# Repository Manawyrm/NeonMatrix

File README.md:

NeonMatrix
=============================

#### Overview

The NeonMatrix 8x8 matrix uses common neon indicator bulbs to display simple graphics.  
They can be chained and controlled directly via SPI.  

Operating voltage is about ~70V AC.  
The circuit is **pretty dangerous**, all neon bulbs have high voltages on their legs, the 74HC595 shift registers are floating at mains/AC potential.  
Safe data in/output is realized through 3 ADUM1200 digital isolator ICs and one B0505S DC-DC isolating converter. 

#### Additional info

[Firmware](https://github.com/Manawyrm/NeonMatrix-Firmware)  
[Schematic](https://github.com/Manawyrm/NeonMatrix/blob/master/Schematic.pdf)

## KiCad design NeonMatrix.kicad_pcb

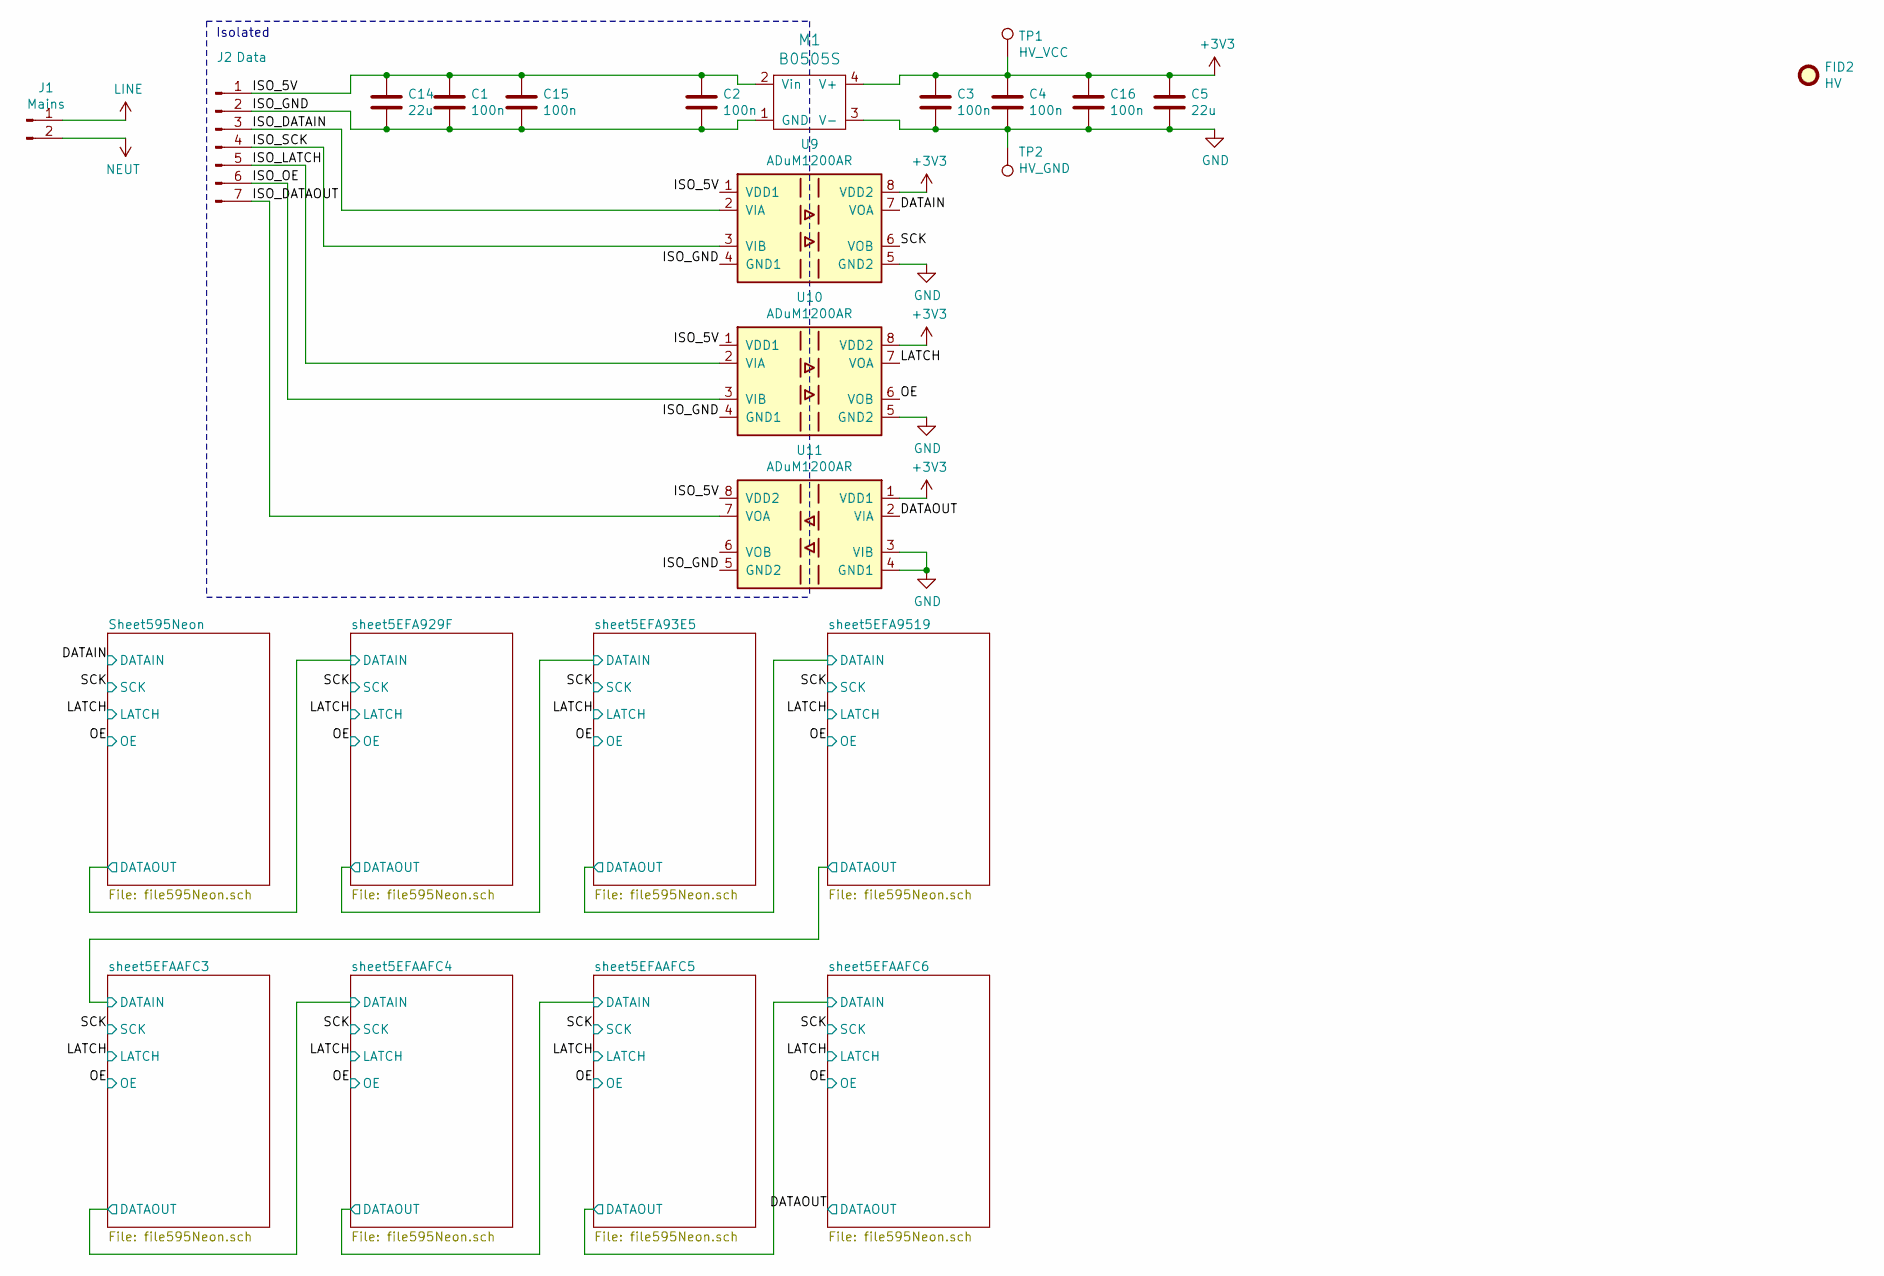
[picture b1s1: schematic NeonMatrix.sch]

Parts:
C1, C2, C3, C4, C15, C16: 100n; C_0805_2012Metric; LCSC C49678
C5, C14: 22u; C_0805_2012Metric; LCSC C45783
FID2: HV; Symbol_HighVoltage_Type1_CopperTop_Big
J1: Mains; TerminalBlock_RND_205-00001_1x02_P5.00mm_Horizontal
J2: Data; PinHeader_1x07_P2.54mm_Vertical
M1: B0505S; M_DCDC_SIP4
TP1: HV_VCC; TestPoint_Pad_2.0x2.0mm
TP2: HV_GND; TestPoint_Pad_2.0x2.0mm
U9, U10, U11: ADuM1200AR; SOIC-8_3.9x4.9mm_P1.27mm; LCSC C15219

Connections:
+3V3: C3.1, C4.1, C5.1, C16.1, M1.4 (V+), TP1.1, U9.8 (VDD2), U10.8 (VDD2), U11.1 (VDD1); also elsewhere on the board
/DATAIN: U9.7 (VOA); also elsewhere on the board
/DATAOUT: U11.2 (VIA); also elsewhere on the board
/ISO_5V: C1.1, C2.1, C14.1, C15.1, J2.1, M1.2 (Vin), U9.1 (VDD1), U10.1 (VDD1), U11.8 (VDD2)
/ISO_DATAIN: J2.3, U9.2 (VIA)
/ISO_DATAOUT: J2.7, U11.7 (VOA)
/ISO_GND: C1.2, C2.2, C14.2, C15.2, J2.2, M1.1 (GND), U9.4 (GND1), U10.4 (GND1), U11.5 (GND2)
/ISO_LATCH: J2.5, U10.2 (VIA)
/ISO_OE: J2.6, U10.3 (VIB)
/ISO_SCK: J2.4, U9.3 (VIB)
/LATCH: U10.7 (VOA); also elsewhere on the board
/OE: U10.6 (VOB); also elsewhere on the board
/SCK: U9.6 (VOB); also elsewhere on the board
GND: C3.2, C4.2, C5.2, C16.2, J1.2, M1.3 (V-), TP2.1, U9.5 (GND2), U10.5 (GND2), U11.3 (VIB), U11.4 (GND1); also elsewhere on the board
LINE: J1.1; also elsewhere on the board

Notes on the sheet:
Isolated

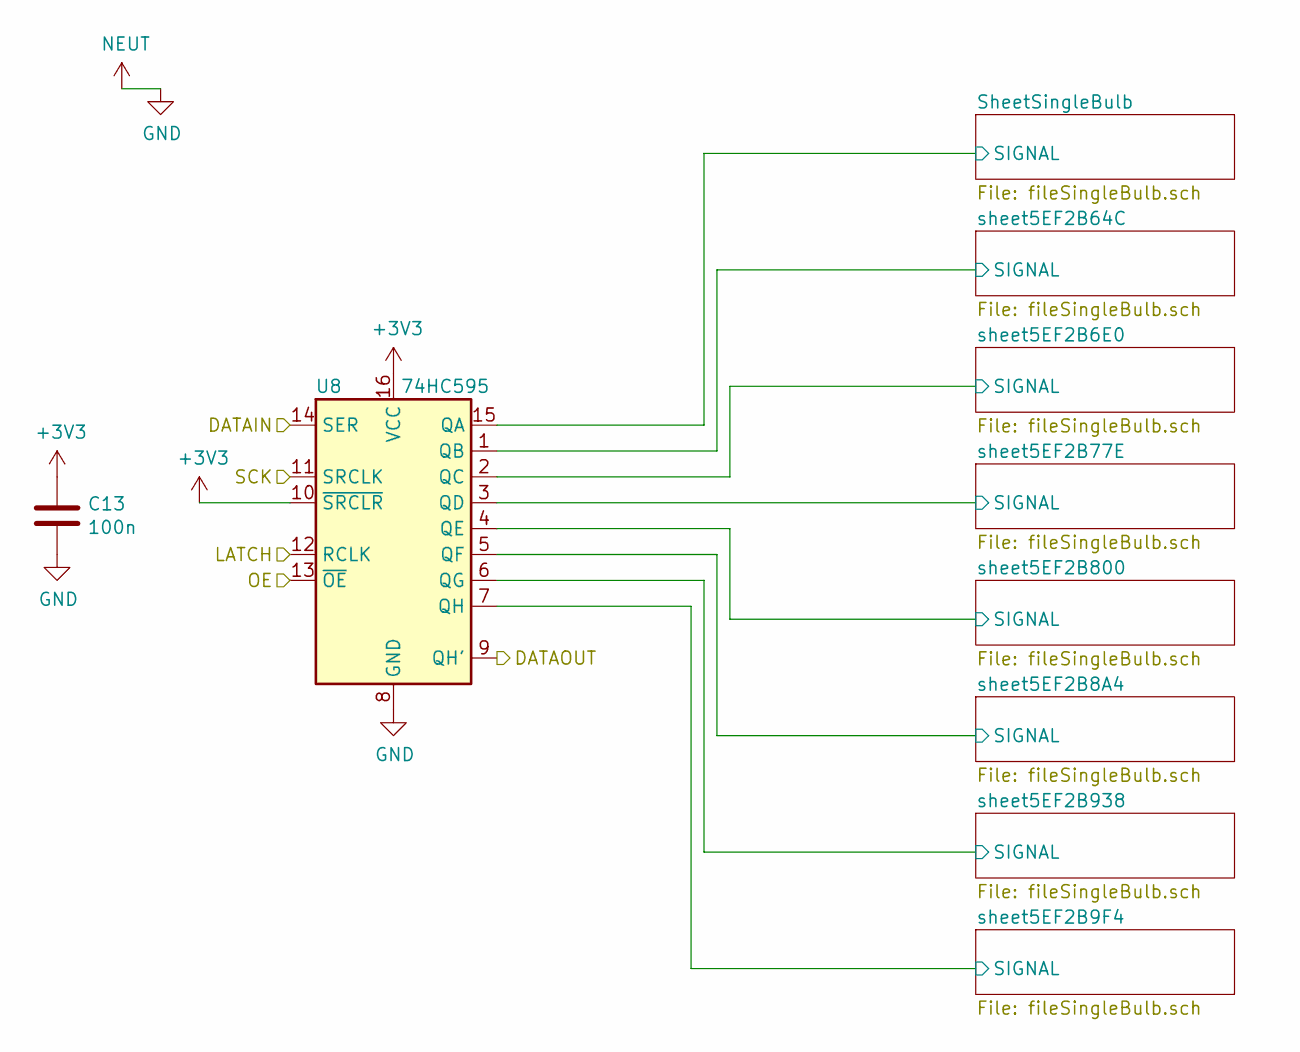
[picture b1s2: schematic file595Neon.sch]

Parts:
C7: 100n; C_0805_2012Metric; LCSC C49678
U1: 74HC595; SOIC-16_3.9x9.9mm_P1.27mm; LCSC C5947

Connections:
+3V3: C7.1, U1.10 (~SRCLR), U1.16 (VCC); also elsewhere on the board
/DATAIN: U1.14 (SER); also elsewhere on the board
/LATCH: U1.12 (RCLK); also elsewhere on the board
/OE: U1.13 (~OE); also elsewhere on the board
/SCK: U1.11 (SRCLK); also elsewhere on the board
/Sheet595Neon/SheetSingleBulb/SIGNAL: U1.15 (QA); also elsewhere on the board
/Sheet595Neon/sheet5EF2B6E0/SIGNAL: U1.2 (QC); also elsewhere on the board
/Sheet595Neon/sheet5EF2B8A4/SIGNAL: U1.5 (QF); also elsewhere on the board
/Sheet595Neon/sheet5EF2B9F4/SIGNAL: U1.7 (QH); also elsewhere on the board
/Sheet595Neon/sheet5EF2B64C/SIGNAL: U1.1 (QB); also elsewhere on the board
/Sheet595Neon/sheet5EF2B77E/SIGNAL: U1.3 (QD); also elsewhere on the board
/Sheet595Neon/sheet5EF2B800/SIGNAL: U1.4 (QE); also elsewhere on the board
/Sheet595Neon/sheet5EF2B938/SIGNAL: U1.6 (QG); also elsewhere on the board
/sheet5EFA929F/DATAIN: U1.9 (QH'); also elsewhere on the board
GND: C7.2, U1.8 (GND); also elsewhere on the board

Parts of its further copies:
C6, C8, C9, C10, C11, C12, C13: 100n; C_0805_2012Metric; LCSC C49678
U2, U3, U4, U5, U6, U7, U8: 74HC595; SOIC-16_3.9x9.9mm_P1.27mm; LCSC C5947

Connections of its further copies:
+3V3: C6.1, C8.1, C9.1, C10.1, C11.1, C12.1, C13.1, U2.10 (~SRCLR), U2.16 (VCC), U3.10 (~SRCLR), U3.16 (VCC), U4.10 (~SRCLR), U4.16 (VCC), U5.10 (~SRCLR), U5.16 (VCC), U6.10 (~SRCLR), U6.16 (VCC), U7.10 (~SRCLR), U7.16 (VCC), U8.10 (~SRCLR), U8.16 (VCC); also elsewhere on the board
/DATAOUT: U8.9 (QH'); also elsewhere on the board
/LATCH: U2.12 (RCLK), U3.12 (RCLK), U4.12 (RCLK), U5.12 (RCLK), U6.12 (RCLK), U7.12 (RCLK), U8.12 (RCLK); also elsewhere on the board
/OE: U2.13 (~OE), U3.13 (~OE), U4.13 (~OE), U5.13 (~OE), U6.13 (~OE), U7.13 (~OE), U8.13 (~OE); also elsewhere on the board
/SCK: U2.11 (SRCLK), U3.11 (SRCLK), U4.11 (SRCLK), U5.11 (SRCLK), U6.11 (SRCLK), U7.11 (SRCLK), U8.11 (SRCLK); also elsewhere on the board
/sheet5EFA93E5/DATAIN: U2.9 (QH'), U3.14 (SER)
/sheet5EFA93E5/SheetSingleBulb/SIGNAL: U3.15 (QA); also elsewhere on the board
/sheet5EFA93E5/sheet5EF2B6E0/SIGNAL: U3.2 (QC); also elsewhere on the board
/sheet5EFA93E5/sheet5EF2B8A4/SIGNAL: U3.5 (QF); also elsewhere on the board
/sheet5EFA93E5/sheet5EF2B9F4/SIGNAL: U3.7 (QH); also elsewhere on the board
/sheet5EFA93E5/sheet5EF2B64C/SIGNAL: U3.1 (QB); also elsewhere on the board
/sheet5EFA93E5/sheet5EF2B77E/SIGNAL: U3.3 (QD); also elsewhere on the board
/sheet5EFA93E5/sheet5EF2B800/SIGNAL: U3.4 (QE); also elsewhere on the board
/sheet5EFA93E5/sheet5EF2B938/SIGNAL: U3.6 (QG); also elsewhere on the board
/sheet5EFA929F/DATAIN: U2.14 (SER); also elsewhere on the board
/sheet5EFA929F/SheetSingleBulb/SIGNAL: U2.15 (QA); also elsewhere on the board
/sheet5EFA929F/sheet5EF2B6E0/SIGNAL: U2.2 (QC); also elsewhere on the board
/sheet5EFA929F/sheet5EF2B8A4/SIGNAL: U2.5 (QF); also elsewhere on the board
/sheet5EFA929F/sheet5EF2B9F4/SIGNAL: U2.7 (QH); also elsewhere on the board
/sheet5EFA929F/sheet5EF2B64C/SIGNAL: U2.1 (QB); also elsewhere on the board
/sheet5EFA929F/sheet5EF2B77E/SIGNAL: U2.3 (QD); also elsewhere on the board
/sheet5EFA929F/sheet5EF2B800/SIGNAL: U2.4 (QE); also elsewhere on the board
/sheet5EFA929F/sheet5EF2B938/SIGNAL: U2.6 (QG); also elsewhere on the board
/sheet5EFA9519/DATAIN: U3.9 (QH'), U4.14 (SER)
/sheet5EFA9519/SheetSingleBulb/SIGNAL: U4.15 (QA); also elsewhere on the board
/sheet5EFA9519/sheet5EF2B6E0/SIGNAL: U4.2 (QC); also elsewhere on the board
/sheet5EFA9519/sheet5EF2B8A4/SIGNAL: U4.5 (QF); also elsewhere on the board
/sheet5EFA9519/sheet5EF2B9F4/SIGNAL: U4.7 (QH); also elsewhere on the board
/sheet5EFA9519/sheet5EF2B64C/SIGNAL: U4.1 (QB); also elsewhere on the board
/sheet5EFA9519/sheet5EF2B77E/SIGNAL: U4.3 (QD); also elsewhere on the board
/sheet5EFA9519/sheet5EF2B800/SIGNAL: U4.4 (QE); also elsewhere on the board
/sheet5EFA9519/sheet5EF2B938/SIGNAL: U4.6 (QG); also elsewhere on the board
/sheet5EFAAFC3/DATAIN: U4.9 (QH'), U5.14 (SER)
/sheet5EFAAFC3/SheetSingleBulb/SIGNAL: U5.15 (QA); also elsewhere on the board
/sheet5EFAAFC3/sheet5EF2B6E0/SIGNAL: U5.2 (QC); also elsewhere on the board
/sheet5EFAAFC3/sheet5EF2B8A4/SIGNAL: U5.5 (QF); also elsewhere on the board
/sheet5EFAAFC3/sheet5EF2B9F4/SIGNAL: U5.7 (QH); also elsewhere on the board
/sheet5EFAAFC3/sheet5EF2B64C/SIGNAL: U5.1 (QB); also elsewhere on the board
/sheet5EFAAFC3/sheet5EF2B77E/SIGNAL: U5.3 (QD); also elsewhere on the board
/sheet5EFAAFC3/sheet5EF2B800/SIGNAL: U5.4 (QE); also elsewhere on the board
/sheet5EFAAFC3/sheet5EF2B938/SIGNAL: U5.6 (QG); also elsewhere on the board
/sheet5EFAAFC4/DATAIN: U5.9 (QH'), U6.14 (SER)
/sheet5EFAAFC4/SheetSingleBulb/SIGNAL: U6.15 (QA); also elsewhere on the board
/sheet5EFAAFC4/sheet5EF2B6E0/SIGNAL: U6.2 (QC); also elsewhere on the board
/sheet5EFAAFC4/sheet5EF2B8A4/SIGNAL: U6.5 (QF); also elsewhere on the board
/sheet5EFAAFC4/sheet5EF2B9F4/SIGNAL: U6.7 (QH); also elsewhere on the board
/sheet5EFAAFC4/sheet5EF2B64C/SIGNAL: U6.1 (QB); also elsewhere on the board
/sheet5EFAAFC4/sheet5EF2B77E/SIGNAL: U6.3 (QD); also elsewhere on the board
/sheet5EFAAFC4/sheet5EF2B800/SIGNAL: U6.4 (QE); also elsewhere on the board
/sheet5EFAAFC4/sheet5EF2B938/SIGNAL: U6.6 (QG); also elsewhere on the board
/sheet5EFAAFC5/DATAIN: U6.9 (QH'), U7.14 (SER)
/sheet5EFAAFC5/SheetSingleBulb/SIGNAL: U7.15 (QA); also elsewhere on the board
/sheet5EFAAFC5/sheet5EF2B6E0/SIGNAL: U7.2 (QC); also elsewhere on the board
/sheet5EFAAFC5/sheet5EF2B8A4/SIGNAL: U7.5 (QF); also elsewhere on the board
/sheet5EFAAFC5/sheet5EF2B9F4/SIGNAL: U7.7 (QH); also elsewhere on the board
/sheet5EFAAFC5/sheet5EF2B64C/SIGNAL: U7.1 (QB); also elsewhere on the board
/sheet5EFAAFC5/sheet5EF2B77E/SIGNAL: U7.3 (QD); also elsewhere on the board
/sheet5EFAAFC5/sheet5EF2B800/SIGNAL: U7.4 (QE); also elsewhere on the board
/sheet5EFAAFC5/sheet5EF2B938/SIGNAL: U7.6 (QG); also elsewhere on the board
/sheet5EFAAFC6/DATAIN: U7.9 (QH'), U8.14 (SER)
/sheet5EFAAFC6/SheetSingleBulb/SIGNAL: U8.15 (QA); also elsewhere on the board
/sheet5EFAAFC6/sheet5EF2B6E0/SIGNAL: U8.2 (QC); also elsewhere on the board
/sheet5EFAAFC6/sheet5EF2B8A4/SIGNAL: U8.5 (QF); also elsewhere on the board
/sheet5EFAAFC6/sheet5EF2B9F4/SIGNAL: U8.7 (QH); also elsewhere on the board
/sheet5EFAAFC6/sheet5EF2B64C/SIGNAL: U8.1 (QB); also elsewhere on the board
/sheet5EFAAFC6/sheet5EF2B77E/SIGNAL: U8.3 (QD); also elsewhere on the board
/sheet5EFAAFC6/sheet5EF2B800/SIGNAL: U8.4 (QE); also elsewhere on the board
/sheet5EFAAFC6/sheet5EF2B938/SIGNAL: U8.6 (QG); also elsewhere on the board
GND: C6.2, C8.2, C9.2, C10.2, C11.2, C12.2, C13.2, U2.8 (GND), U3.8 (GND), U4.8 (GND), U5.8 (GND), U6.8 (GND), U7.8 (GND), U8.8 (GND); also elsewhere on the board

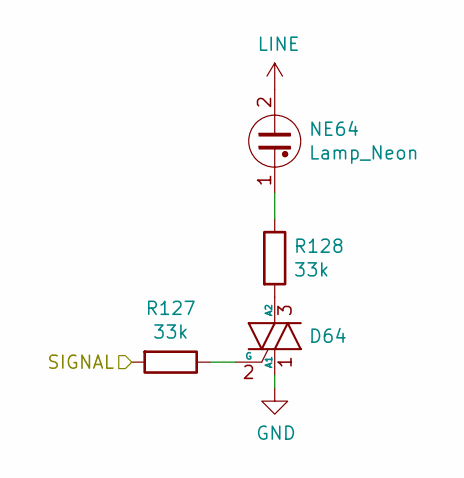
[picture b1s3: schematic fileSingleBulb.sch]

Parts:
D1: Q_TRIAC_A1GA2; SOT-23; LCSC C85116
NE1: Lamp_Neon; NeonBulb
R1: 33k; R_0402_1005Metric; LCSC C25779
R2: 33k; R_0603_1608Metric; LCSC C4216

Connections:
/Sheet595Neon/SheetSingleBulb/SIGNAL: R1.2; also elsewhere on the board
GND: D1.1 (A1); also elsewhere on the board
LINE: NE1.2; also elsewhere on the board
unnamed: D1.2 (G), R1.1
unnamed: D1.3 (A2), R2.2
unnamed: NE1.1, R2.1

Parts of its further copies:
D2, D3, D4, D5, D6, D7, D8, D9, D10, D11, D12, D13, D14, D15, D16, D17, D18, D19, D20, D21, D22, D23, D24, D25, D26, D27, D28, D29, D30, D31, D32, D33, D34, D35, D36, D37, D38, D39, D40, D41, D42, D43, D44, D45, D46, D47, D48, D49, D50, D51, D52, D53, D54, D55, D56, D57, D58, D59, D60, D61, D62, D63, D64: Q_TRIAC_A1GA2; SOT-23; LCSC C85116
NE2, NE3, NE4, NE5, NE6, NE7, NE8, NE9, NE10, NE11, NE12, NE13, NE14, NE15, NE16, NE17, NE18, NE19, NE20, NE21, NE22, NE23, NE24, NE25, NE26, NE27, NE28, NE29, NE30, NE31, NE32, NE33, NE34, NE35, NE36, NE37, NE38, NE39, NE40, NE41, NE42, NE43, NE44, NE45, NE46, NE47, NE48, NE49, NE50, NE51, NE52, NE53, NE54, NE55, NE56, NE57, NE58, NE59, NE60, NE61, NE62, NE63, NE64: Lamp_Neon; NeonBulb
R3, R5, R7, R9, R11, R13, R15, R17, R19, R21, R23, R25, R27, R29, R31, R33, R35, R37, R39, R41, R43, R45, R47, R49, R51, R53, R55, R57, R59, R61, R63, R65, R67, R69, R71, R73, R75, R77, R79, R81, R83, R85, R87, R89, R91, R93, R95, R97, R99, R101, R103, R105, R107, R109, R111, R113, R115, R117, R119, R121, R123, R125, R127: 33k; R_0402_1005Metric; LCSC C25779
R4, R6, R8, R10, R12, R14, R16, R18, R20, R22, R24, R26, R28, R30, R32, R34, R36, R38, R40, R42, R44, R46, R48, R50, R52, R54, R56, R58, R60, R62, R64, R66, R68, R70, R72, R74, R76, R78, R80, R82, R84, R86, R88, R90, R92, R94, R96, R98, R100, R102, R104, R106, R108, R110, R112, R114, R116, R118, R120, R122, R124, R126, R128: 33k; R_0603_1608Metric; LCSC C4216

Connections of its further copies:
/Sheet595Neon/sheet5EF2B6E0/SIGNAL: R5.2; also elsewhere on the board
/Sheet595Neon/sheet5EF2B8A4/SIGNAL: R11.2; also elsewhere on the board
/Sheet595Neon/sheet5EF2B9F4/SIGNAL: R15.2; also elsewhere on the board
/Sheet595Neon/sheet5EF2B64C/SIGNAL: R3.2; also elsewhere on the board
/Sheet595Neon/sheet5EF2B77E/SIGNAL: R7.2; also elsewhere on the board
/Sheet595Neon/sheet5EF2B800/SIGNAL: R9.2; also elsewhere on the board
/Sheet595Neon/sheet5EF2B938/SIGNAL: R13.2; also elsewhere on the board
/sheet5EFA93E5/SheetSingleBulb/SIGNAL: R33.2; also elsewhere on the board
/sheet5EFA93E5/sheet5EF2B6E0/SIGNAL: R37.2; also elsewhere on the board
/sheet5EFA93E5/sheet5EF2B8A4/SIGNAL: R43.2; also elsewhere on the board
/sheet5EFA93E5/sheet5EF2B9F4/SIGNAL: R47.2; also elsewhere on the board
/sheet5EFA93E5/sheet5EF2B64C/SIGNAL: R35.2; also elsewhere on the board
/sheet5EFA93E5/sheet5EF2B77E/SIGNAL: R39.2; also elsewhere on the board
/sheet5EFA93E5/sheet5EF2B800/SIGNAL: R41.2; also elsewhere on the board
/sheet5EFA93E5/sheet5EF2B938/SIGNAL: R45.2; also elsewhere on the board
/sheet5EFA929F/SheetSingleBulb/SIGNAL: R17.2; also elsewhere on the board
/sheet5EFA929F/sheet5EF2B6E0/SIGNAL: R21.2; also elsewhere on the board
/sheet5EFA929F/sheet5EF2B8A4/SIGNAL: R27.2; also elsewhere on the board
/sheet5EFA929F/sheet5EF2B9F4/SIGNAL: R31.2; also elsewhere on the board
/sheet5EFA929F/sheet5EF2B64C/SIGNAL: R19.2; also elsewhere on the board
/sheet5EFA929F/sheet5EF2B77E/SIGNAL: R23.2; also elsewhere on the board
/sheet5EFA929F/sheet5EF2B800/SIGNAL: R25.2; also elsewhere on the board
/sheet5EFA929F/sheet5EF2B938/SIGNAL: R29.2; also elsewhere on the board
/sheet5EFA9519/SheetSingleBulb/SIGNAL: R49.2; also elsewhere on the board
/sheet5EFA9519/sheet5EF2B6E0/SIGNAL: R53.2; also elsewhere on the board
/sheet5EFA9519/sheet5EF2B8A4/SIGNAL: R59.2; also elsewhere on the board
/sheet5EFA9519/sheet5EF2B9F4/SIGNAL: R63.2; also elsewhere on the board
/sheet5EFA9519/sheet5EF2B64C/SIGNAL: R51.2; also elsewhere on the board
/sheet5EFA9519/sheet5EF2B77E/SIGNAL: R55.2; also elsewhere on the board
/sheet5EFA9519/sheet5EF2B800/SIGNAL: R57.2; also elsewhere on the board
/sheet5EFA9519/sheet5EF2B938/SIGNAL: R61.2; also elsewhere on the board
/sheet5EFAAFC3/SheetSingleBulb/SIGNAL: R65.2; also elsewhere on the board
/sheet5EFAAFC3/sheet5EF2B6E0/SIGNAL: R69.2; also elsewhere on the board
/sheet5EFAAFC3/sheet5EF2B8A4/SIGNAL: R75.2; also elsewhere on the board
/sheet5EFAAFC3/sheet5EF2B9F4/SIGNAL: R79.2; also elsewhere on the board
/sheet5EFAAFC3/sheet5EF2B64C/SIGNAL: R67.2; also elsewhere on the board
/sheet5EFAAFC3/sheet5EF2B77E/SIGNAL: R71.2; also elsewhere on the board
/sheet5EFAAFC3/sheet5EF2B800/SIGNAL: R73.2; also elsewhere on the board
/sheet5EFAAFC3/sheet5EF2B938/SIGNAL: R77.2; also elsewhere on the board
/sheet5EFAAFC4/SheetSingleBulb/SIGNAL: R81.2; also elsewhere on the board
/sheet5EFAAFC4/sheet5EF2B6E0/SIGNAL: R85.2; also elsewhere on the board
/sheet5EFAAFC4/sheet5EF2B8A4/SIGNAL: R91.2; also elsewhere on the board
/sheet5EFAAFC4/sheet5EF2B9F4/SIGNAL: R95.2; also elsewhere on the board
/sheet5EFAAFC4/sheet5EF2B64C/SIGNAL: R83.2; also elsewhere on the board
/sheet5EFAAFC4/sheet5EF2B77E/SIGNAL: R87.2; also elsewhere on the board
/sheet5EFAAFC4/sheet5EF2B800/SIGNAL: R89.2; also elsewhere on the board
/sheet5EFAAFC4/sheet5EF2B938/SIGNAL: R93.2; also elsewhere on the board
/sheet5EFAAFC5/SheetSingleBulb/SIGNAL: R97.2; also elsewhere on the board
/sheet5EFAAFC5/sheet5EF2B6E0/SIGNAL: R101.2; also elsewhere on the board
/sheet5EFAAFC5/sheet5EF2B8A4/SIGNAL: R107.2; also elsewhere on the board
/sheet5EFAAFC5/sheet5EF2B9F4/SIGNAL: R111.2; also elsewhere on the board
/sheet5EFAAFC5/sheet5EF2B64C/SIGNAL: R99.2; also elsewhere on the board
/sheet5EFAAFC5/sheet5EF2B77E/SIGNAL: R103.2; also elsewhere on the board
/sheet5EFAAFC5/sheet5EF2B800/SIGNAL: R105.2; also elsewhere on the board
/sheet5EFAAFC5/sheet5EF2B938/SIGNAL: R109.2; also elsewhere on the board
/sheet5EFAAFC6/SheetSingleBulb/SIGNAL: R113.2; also elsewhere on the board
/sheet5EFAAFC6/sheet5EF2B6E0/SIGNAL: R117.2; also elsewhere on the board
/sheet5EFAAFC6/sheet5EF2B8A4/SIGNAL: R123.2; also elsewhere on the board
/sheet5EFAAFC6/sheet5EF2B9F4/SIGNAL: R127.2; also elsewhere on the board
/sheet5EFAAFC6/sheet5EF2B64C/SIGNAL: R115.2; also elsewhere on the board
/sheet5EFAAFC6/sheet5EF2B77E/SIGNAL: R119.2; also elsewhere on the board
/sheet5EFAAFC6/sheet5EF2B800/SIGNAL: R121.2; also elsewhere on the board
/sheet5EFAAFC6/sheet5EF2B938/SIGNAL: R125.2; also elsewhere on the board
GND: D2.1 (A1), D3.1 (A1), D4.1 (A1), D5.1 (A1), D6.1 (A1), D7.1 (A1), D8.1 (A1), D9.1 (A1), D10.1 (A1), D11.1 (A1), D12.1 (A1), D13.1 (A1), D14.1 (A1), D15.1 (A1), D16.1 (A1), D17.1 (A1), D18.1 (A1), D19.1 (A1), D20.1 (A1), D21.1 (A1), D22.1 (A1), D23.1 (A1), D24.1 (A1), D25.1 (A1), D26.1 (A1), D27.1 (A1), D28.1 (A1), D29.1 (A1), D30.1 (A1), D31.1 (A1), D32.1 (A1), D33.1 (A1), D34.1 (A1), D35.1 (A1), D36.1 (A1), D37.1 (A1), D38.1 (A1), D39.1 (A1), D40.1 (A1), D41.1 (A1), D42.1 (A1), D43.1 (A1), D44.1 (A1), D45.1 (A1), D46.1 (A1), D47.1 (A1), D48.1 (A1), D49.1 (A1), D50.1 (A1), D51.1 (A1), D52.1 (A1), D53.1 (A1), D54.1 (A1), D55.1 (A1), D56.1 (A1), D57.1 (A1), D58.1 (A1), D59.1 (A1), D60.1 (A1), D61.1 (A1), D62.1 (A1), D63.1 (A1), D64.1 (A1); also elsewhere on the board
LINE: NE2.2, NE3.2, NE4.2, NE5.2, NE6.2, NE7.2, NE8.2, NE9.2, NE10.2, NE11.2, NE12.2, NE13.2, NE14.2, NE15.2, NE16.2, NE17.2, NE18.2, NE19.2, NE20.2, NE21.2, NE22.2, NE23.2, NE24.2, NE25.2, NE26.2, NE27.2, NE28.2, NE29.2, NE30.2, NE31.2, NE32.2, NE33.2, NE34.2, NE35.2, NE36.2, NE37.2, NE38.2, NE39.2, NE40.2, NE41.2, NE42.2, NE43.2, NE44.2, NE45.2, NE46.2, NE47.2, NE48.2, NE49.2, NE50.2, NE51.2, NE52.2, NE53.2, NE54.2, NE55.2, NE56.2, NE57.2, NE58.2, NE59.2, NE60.2, NE61.2, NE62.2, NE63.2, NE64.2; also elsewhere on the board
unnamed: D2.2 (G), R3.1
unnamed: D2.3 (A2), R4.2
unnamed: D3.2 (G), R5.1
unnamed: D3.3 (A2), R6.2
unnamed: D4.2 (G), R7.1
unnamed: D4.3 (A2), R8.2
unnamed: D5.2 (G), R9.1
unnamed: D5.3 (A2), R10.2
unnamed: D6.2 (G), R11.1
unnamed: D6.3 (A2), R12.2
unnamed: D7.2 (G), R13.1
unnamed: D7.3 (A2), R14.2
unnamed: D8.2 (G), R15.1
unnamed: D8.3 (A2), R16.2
unnamed: D9.2 (G), R17.1
unnamed: D9.3 (A2), R18.2
unnamed: D10.2 (G), R19.1
unnamed: D10.3 (A2), R20.2
unnamed: D11.2 (G), R21.1
unnamed: D11.3 (A2), R22.2
unnamed: D12.2 (G), R23.1
unnamed: D12.3 (A2), R24.2
unnamed: D13.2 (G), R25.1
unnamed: D13.3 (A2), R26.2
unnamed: D14.2 (G), R27.1
unnamed: D14.3 (A2), R28.2
unnamed: D15.2 (G), R29.1
unnamed: D15.3 (A2), R30.2
unnamed: D16.2 (G), R31.1
unnamed: D16.3 (A2), R32.2
unnamed: D17.2 (G), R33.1
unnamed: D17.3 (A2), R34.2
unnamed: D18.2 (G), R35.1
unnamed: D18.3 (A2), R36.2
unnamed: D19.2 (G), R37.1
unnamed: D19.3 (A2), R38.2
unnamed: D20.2 (G), R39.1
unnamed: D20.3 (A2), R40.2
unnamed: D21.2 (G), R41.1
unnamed: D21.3 (A2), R42.2
unnamed: D22.2 (G), R43.1
unnamed: D22.3 (A2), R44.2
unnamed: D23.2 (G), R45.1
unnamed: D23.3 (A2), R46.2
unnamed: D24.2 (G), R47.1
unnamed: D24.3 (A2), R48.2
unnamed: D25.2 (G), R49.1
unnamed: D25.3 (A2), R50.2
unnamed: D26.2 (G), R51.1
unnamed: D26.3 (A2), R52.2
unnamed: D27.2 (G), R53.1
unnamed: D27.3 (A2), R54.2
unnamed: D28.2 (G), R55.1
unnamed: D28.3 (A2), R56.2
unnamed: D29.2 (G), R57.1
unnamed: D29.3 (A2), R58.2
unnamed: D30.2 (G), R59.1
unnamed: D30.3 (A2), R60.2
unnamed: D31.2 (G), R61.1
unnamed: D31.3 (A2), R62.2
unnamed: D32.2 (G), R63.1
unnamed: D32.3 (A2), R64.2
unnamed: D33.2 (G), R65.1
unnamed: D33.3 (A2), R66.2
unnamed: D34.2 (G), R67.1
unnamed: D34.3 (A2), R68.2
unnamed: D35.2 (G), R69.1
unnamed: D35.3 (A2), R70.2
unnamed: D36.2 (G), R71.1
unnamed: D36.3 (A2), R72.2
unnamed: D37.2 (G), R73.1
unnamed: D37.3 (A2), R74.2
unnamed: D38.2 (G), R75.1
unnamed: D38.3 (A2), R76.2
unnamed: D39.2 (G), R77.1
unnamed: D39.3 (A2), R78.2
unnamed: D40.2 (G), R79.1
unnamed: D40.3 (A2), R80.2
unnamed: D41.2 (G), R81.1
unnamed: D41.3 (A2), R82.2
unnamed: D42.2 (G), R83.1
unnamed: D42.3 (A2), R84.2
unnamed: D43.2 (G), R85.1
unnamed: D43.3 (A2), R86.2
unnamed: D44.2 (G), R87.1
unnamed: D44.3 (A2), R88.2
unnamed: D45.2 (G), R89.1
unnamed: D45.3 (A2), R90.2
unnamed: D46.2 (G), R91.1
unnamed: D46.3 (A2), R92.2
unnamed: D47.2 (G), R93.1
unnamed: D47.3 (A2), R94.2
unnamed: D48.2 (G), R95.1
unnamed: D48.3 (A2), R96.2
unnamed: D49.2 (G), R97.1
unnamed: D49.3 (A2), R98.2
unnamed: D50.2 (G), R99.1
unnamed: D50.3 (A2), R100.2
unnamed: D51.2 (G), R101.1
unnamed: D51.3 (A2), R102.2
unnamed: D52.2 (G), R103.1
unnamed: D52.3 (A2), R104.2
unnamed: D53.2 (G), R105.1
unnamed: D53.3 (A2), R106.2
unnamed: D54.2 (G), R107.1
unnamed: D54.3 (A2), R108.2
unnamed: D55.2 (G), R109.1
unnamed: D55.3 (A2), R110.2
unnamed: D56.2 (G), R111.1
unnamed: D56.3 (A2), R112.2
unnamed: D57.2 (G), R113.1
unnamed: D57.3 (A2), R114.2
unnamed: D58.2 (G), R115.1
unnamed: D58.3 (A2), R116.2
unnamed: D59.2 (G), R117.1
unnamed: D59.3 (A2), R118.2
unnamed: D60.2 (G), R119.1
unnamed: D60.3 (A2), R120.2
unnamed: D61.2 (G), R121.1
unnamed: D61.3 (A2), R122.2
unnamed: D62.2 (G), R123.1
unnamed: D62.3 (A2), R124.2
unnamed: D63.2 (G), R125.1
unnamed: D63.3 (A2), R126.2
unnamed: D64.2 (G), R127.1
unnamed: D64.3 (A2), R128.2
unnamed: NE2.1, R4.1
unnamed: NE3.1, R6.1
unnamed: NE4.1, R8.1
unnamed: NE5.1, R10.1
unnamed: NE6.1, R12.1
unnamed: NE7.1, R14.1
unnamed: NE8.1, R16.1
unnamed: NE9.1, R18.1
unnamed: NE10.1, R20.1
unnamed: NE11.1, R22.1
unnamed: NE12.1, R24.1
unnamed: NE13.1, R26.1
unnamed: NE14.1, R28.1
unnamed: NE15.1, R30.1
unnamed: NE16.1, R32.1
unnamed: NE17.1, R34.1
unnamed: NE18.1, R36.1
unnamed: NE19.1, R38.1
unnamed: NE20.1, R40.1
unnamed: NE21.1, R42.1
unnamed: NE22.1, R44.1
unnamed: NE23.1, R46.1
unnamed: NE24.1, R48.1
unnamed: NE25.1, R50.1
unnamed: NE26.1, R52.1
unnamed: NE27.1, R54.1
unnamed: NE28.1, R56.1
unnamed: NE29.1, R58.1
unnamed: NE30.1, R60.1
unnamed: NE31.1, R62.1
unnamed: NE32.1, R64.1
unnamed: NE33.1, R66.1
unnamed: NE34.1, R68.1
unnamed: NE35.1, R70.1
unnamed: NE36.1, R72.1
unnamed: NE37.1, R74.1
unnamed: NE38.1, R76.1
unnamed: NE39.1, R78.1
unnamed: NE40.1, R80.1
unnamed: NE41.1, R82.1
unnamed: NE42.1, R84.1
unnamed: NE43.1, R86.1
unnamed: NE44.1, R88.1
unnamed: NE45.1, R90.1
unnamed: NE46.1, R92.1
unnamed: NE47.1, R94.1
unnamed: NE48.1, R96.1
unnamed: NE49.1, R98.1
unnamed: NE50.1, R100.1
unnamed: NE51.1, R102.1
unnamed: NE52.1, R104.1
unnamed: NE53.1, R106.1
unnamed: NE54.1, R108.1
unnamed: NE55.1, R110.1
unnamed: NE56.1, R112.1
unnamed: NE57.1, R114.1
unnamed: NE58.1, R116.1
unnamed: NE59.1, R118.1
unnamed: NE60.1, R120.1
unnamed: NE61.1, R122.1
unnamed: NE62.1, R124.1
unnamed: NE63.1, R126.1
unnamed: NE64.1, R128.1

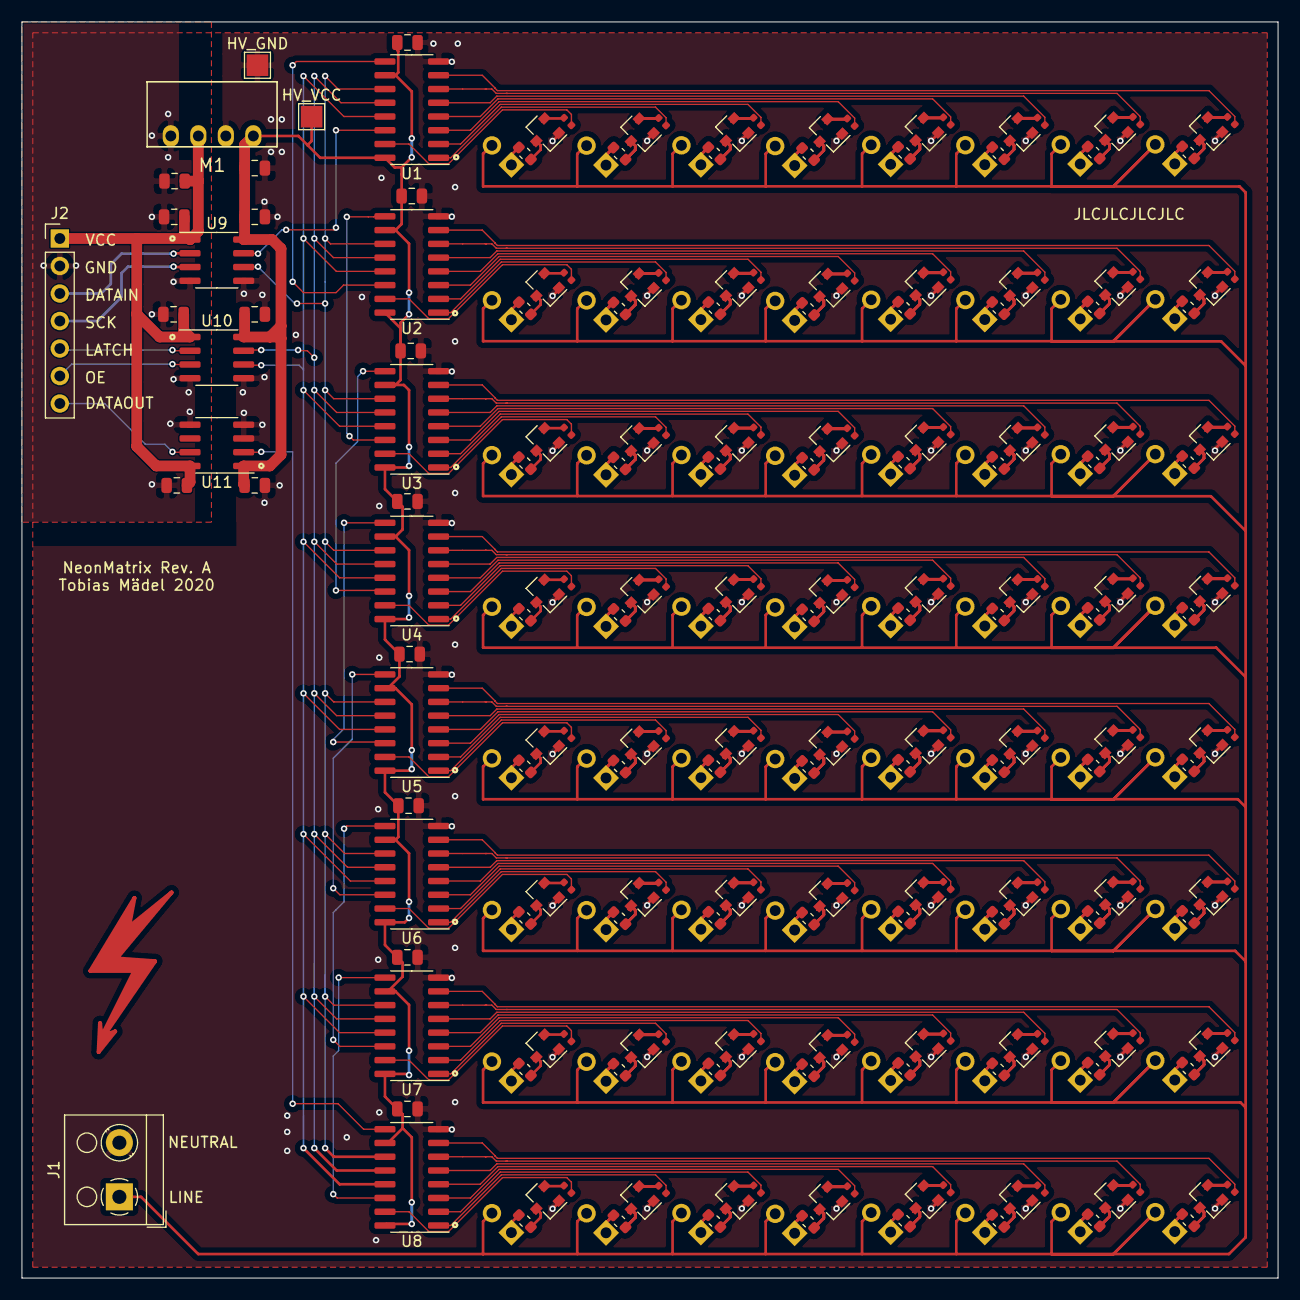
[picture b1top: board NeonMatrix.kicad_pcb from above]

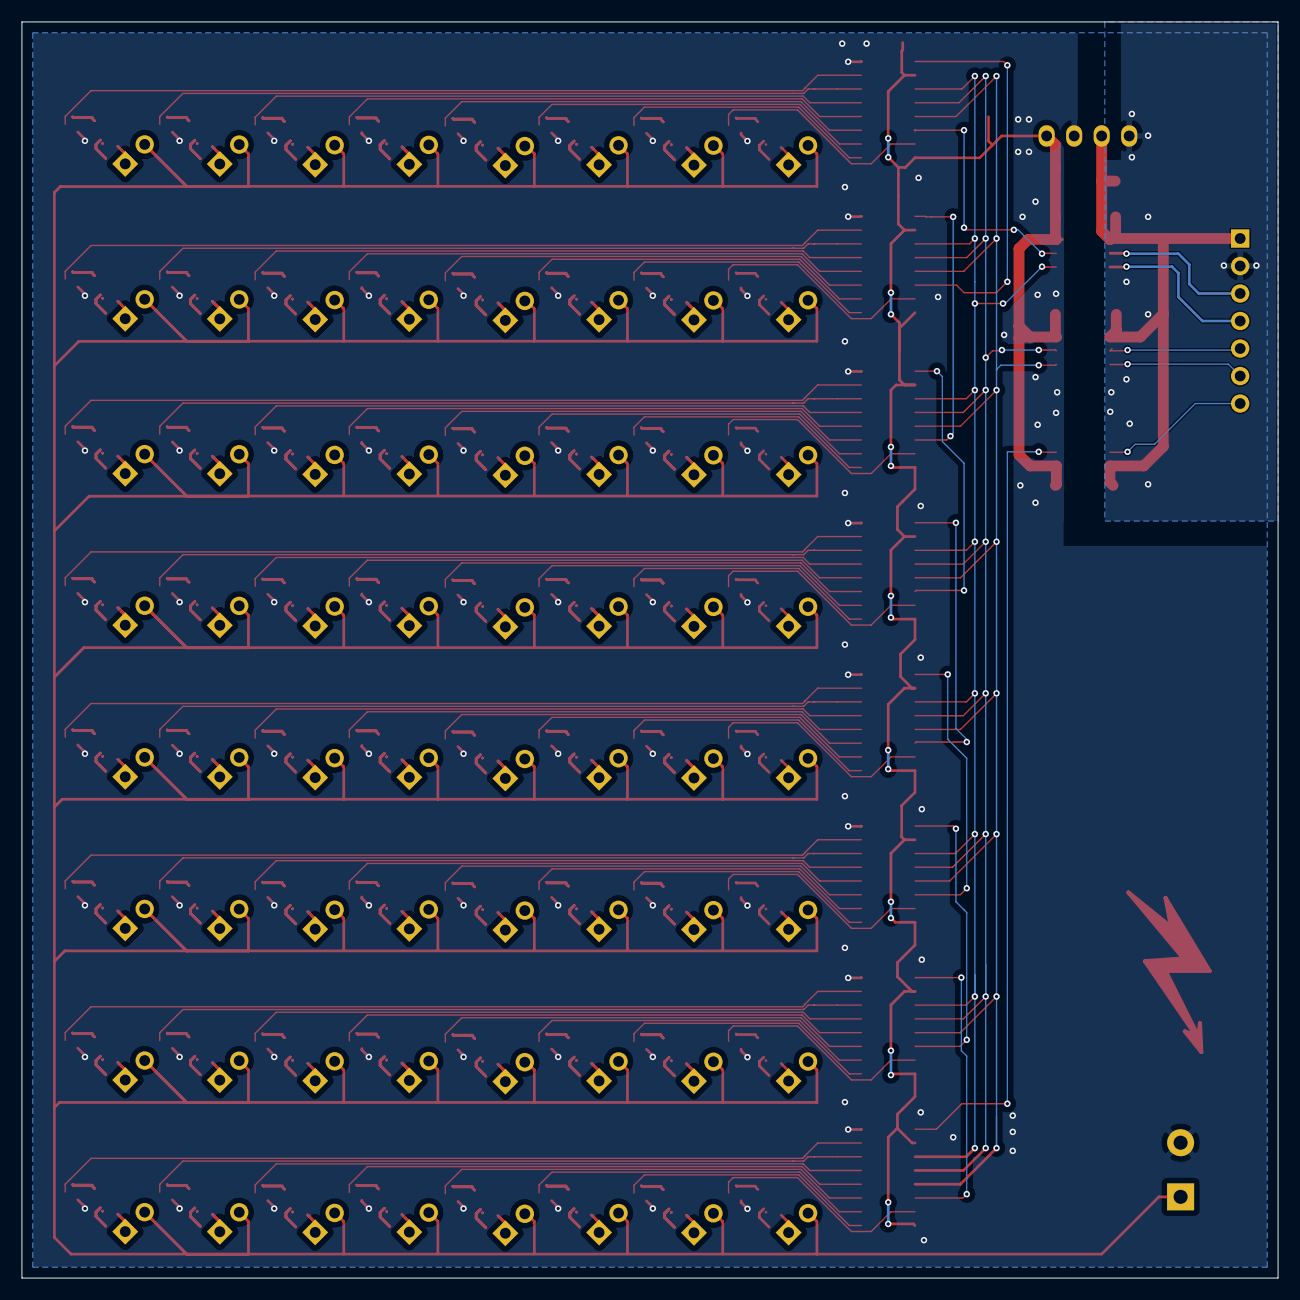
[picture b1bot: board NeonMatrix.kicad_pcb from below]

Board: 2 copper layers, 116.0 x 116.0 mm, 289 parts (64 on the bottom side), 278 nets.

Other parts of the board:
HV_GND: HV_GND; TestPoint_Pad_2.0x2.0mm
HV_VCC: HV_VCC; TestPoint_Pad_2.0x2.0mm

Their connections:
+3V3: HV_VCC.1; also elsewhere on the board
GND: HV_GND.1; also elsewhere on the board

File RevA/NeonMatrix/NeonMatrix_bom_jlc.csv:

"Comment","Designator","Footprint","LCSC Part #"
"100n","C1,C2,C3,C4,C15,C16,C6,C7,C8,C9,C10,C11,C12,C13","C_0805_2012Metric","C49678"
"22u","C5,C14","C_0805_2012Metric","C45783"
"Q_TRIAC_A1GA2","D1,D2,D3,D4,D5,D6,D7,D8,D9,D10,D11,D12,D13,D14,D15,D16,D17,D18,D19,D20,D21,D22,D23,D24,D25,D26,D27,D28,D29,D30,D31,D32,D33,D34,D35,D36,D37,D38,D39,D40,D41,D42,D43,D44,D45,D46,D47,D48,D49,D50,D51,D52,D53,D54,D55,D56,D57,D58,D59,D60,D61,D62,D63,D64","SOT-23","C85116"
"33k","R1,R3,R5,R7,R9,R11,R13,R15,R17,R19,R21,R23,R25,R27,R29,R31,R33,R35,R37,R39,R41,R43,R45,R47,R49,R51,R53,R55,R57,R59,R61,R63,R65,R67,R69,R71,R73,R75,R77,R79,R81,R83,R85,R87,R89,R91,R93,R95,R97,R99,R101,R103,R105,R107,R109,R111,R113,R115,R117,R119,R121,R123,R125,R127","R_0402_1005Metric","C25779"
"33k","R2,R4,R6,R8,R10,R12,R14,R16,R18,R20,R22,R24,R26,R28,R30,R32,R34,R36,R38,R40,R42,R44,R46,R48,R50,R52,R54,R56,R58,R60,R62,R64,R66,R68,R70,R72,R74,R76,R78,R80,R82,R84,R86,R88,R90,R92,R94,R96,R98,R100,R102,R104,R106,R108,R110,R112,R114,R116,R118,R120,R122,R124,R126,R128","R_0603_1608Metric","C4216"
"74HC595","U1,U2,U3,U4,U5,U6,U7,U8","SOIC-16_3.9x9.9mm_P1.27mm","C5947"
"ADuM1200AR","U9,U10,U11","SOIC-8_3.9x4.9mm_P1.27mm","C15219"

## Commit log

2020-06-21 First row
2020-06-23 Add isolation
2020-06-23 Add routing
2020-06-23 Add labels to connectors
2020-06-23 Add PCB markings
2020-06-23 Add bulk capacitance, fix isolation, silkscreen and vias
2020-07-06 RevA, Add production files
2020-07-06 Add Readme, Schematic and images
